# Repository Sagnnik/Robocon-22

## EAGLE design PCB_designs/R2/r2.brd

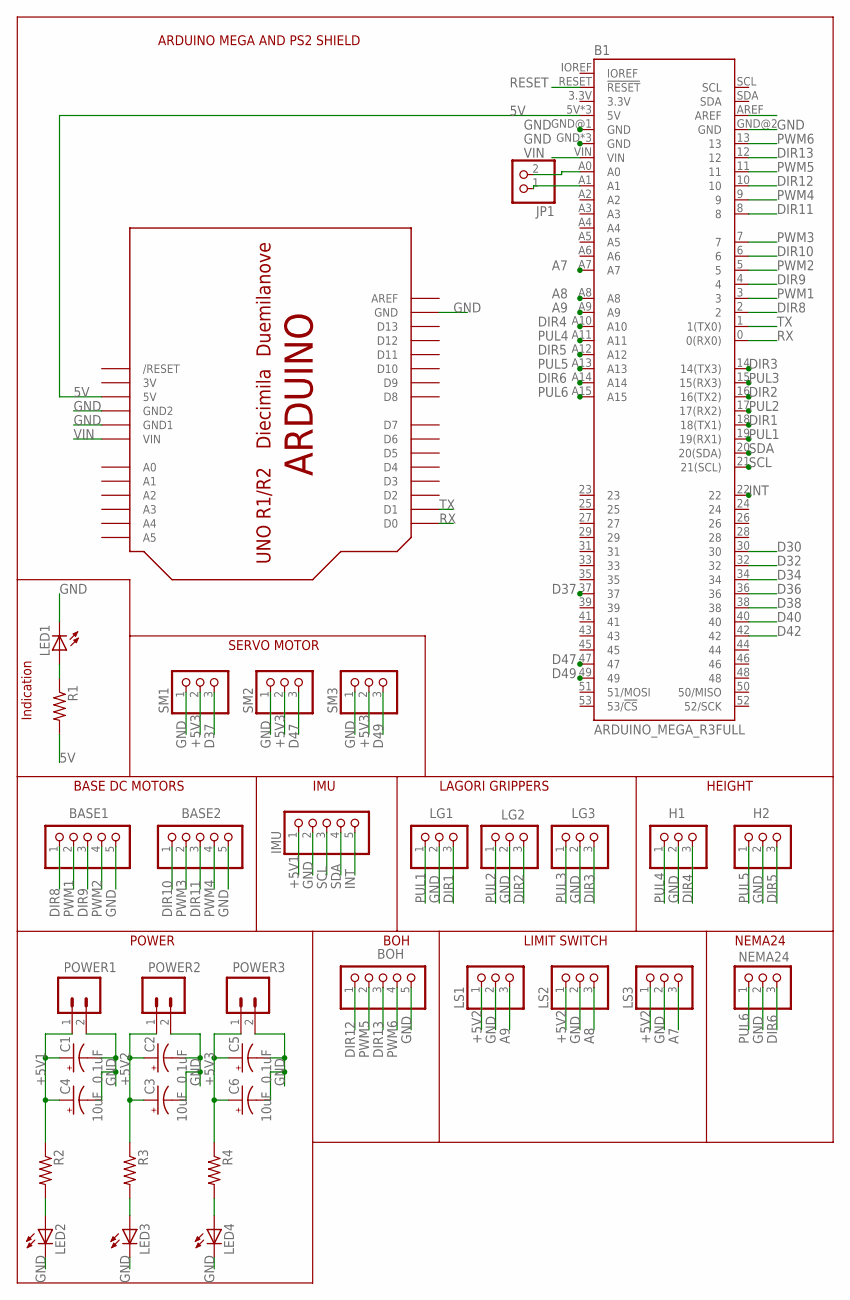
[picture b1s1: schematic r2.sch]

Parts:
B1: ARDUINO_MEGA_R3FULL; ARDUINO_MEGA_NO_SILK
BASE1, BASE2: PINHD-1X5; 1X05
BOH: PINHD-1X5; 1X05
C1, C2, C5: 0.1uF; E2-5
C3, C4, C6: 10uF; E2-5
H1, H2: PINHD-1X3; 1X03
IMU: PINHD-1X5; 1X05
JP1: PINHD-1X2; 1X02
LED1, LED2, LED3, LED4: LED3MM
LG1, LG2, LG3: PINHD-1X3; 1X03
LS1, LS2, LS3: PINHD-1X3; 1X03
NEMA24: PINHD-1X3; 1X03
POWER1, POWER2, POWER3: CONN_02; 1X02
R1, R2, R3, R4: R-US_0204/5; 0204/5
SM1, SM2, SM3: PINHD-1X3; 1X03
U$1: ARDUINO-NOHOLE

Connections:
3V: U$1.3V
5V: B1.5V, B1.5V@1 (5V), B1.5V@2 (5V), R1.2, U$1.5V
+5V1: C1.+, C4.+, IMU.1, POWER1.1, R2.1
+5V2: C2.+, C3.+, LS1.1, LS2.1, LS3.1, POWER2.1, R3.1
+5V3: C5.+, C6.+, POWER3.1, R4.1, SM1.2, SM2.2, SM3.2
A7: B1.A7, LS3.3
A8: B1.A8, LS2.3
A9: B1.A9, LS1.3
D30: B1.30
D32: B1.32
D34: B1.34
D36: B1.36
D37: B1.37, SM1.3
D38: B1.38
D40: B1.40
D42: B1.42
D47: B1.47, SM2.3
D49: B1.49, SM3.3
DIR1: B1.18 (18(TX1)), LG1.3
DIR2: B1.16 (16(TX2)), LG2.3
DIR3: B1.14 (14(TX3)), LG3.3
DIR4: B1.A10, H1.3
DIR5: B1.A12, H2.3
DIR6: B1.A14, NEMA24.3
DIR8: B1.2, BASE1.1
DIR9: B1.4, BASE1.3
DIR10: B1.6, BASE2.1
DIR11: B1.8, BASE2.3
DIR12: B1.10, BOH.1
DIR13: B1.12, BOH.3
GND: B1.GND, B1.GND@1 (GND), B1.GND@2 (GND), B1.GND@3 (GND), B1.GND@4 (GND), BASE1.5, BASE2.5, BOH.5, C1.-, C2.-, C3.-, C4.-, C5.-, C6.-, H1.2, H2.2, IMU.2, LED1.K (C), LED2.K (C), LED3.K (C), LED4.K (C), LG1.2, LG2.2, LG3.2, LS1.2, LS2.2, LS3.2, NEMA24.2, POWER1.2, POWER2.2, POWER3.2, SM1.1, SM2.1, SM3.1, U$1.GND, U$1.GND1, U$1.GND2
INT: B1.22, IMU.5
unnamed: LED1.A, R1.1
unnamed: B1.A0, JP1.2
unnamed: B1.A1, JP1.1
unnamed: LED3.A, R3.2
unnamed: LED4.A, R4.2
unnamed: LED2.A, R2.2
PUL1: B1.19 (19(RX1)), LG1.1
PUL2: B1.17 (17(RX2)), LG2.1
PUL3: B1.15 (15(RX3)), LG3.1
PUL4: B1.A11, H1.1
PUL5: B1.A13, H2.1
PUL6: B1.A15, NEMA24.1
PWM1: B1.3, BASE1.2
PWM2: B1.5, BASE1.4
PWM3: B1.7, BASE2.2
PWM4: B1.9, BASE2.4
PWM5: B1.11, BOH.2
PWM6: B1.13, BOH.4
RESET: B1.RESET (!RESET)
RX: B1.0 (0(RX0)), U$1.D0
SCL: B1.21 (21(SCL)), IMU.3
SDA: B1.20 (20(SDA)), IMU.4
TX: B1.1 (1(TX0)), U$1.D1
VIN: B1.VIN, U$1.VIN

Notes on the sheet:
POWER
BOH
LIMIT SWITCH
LAGORI GRIPPERS
BASE DC MOTORS
ARDUINO MEGA AND PS2 SHIELD
NEMA24
HEIGHT
Indication
IMU
SERVO MOTOR

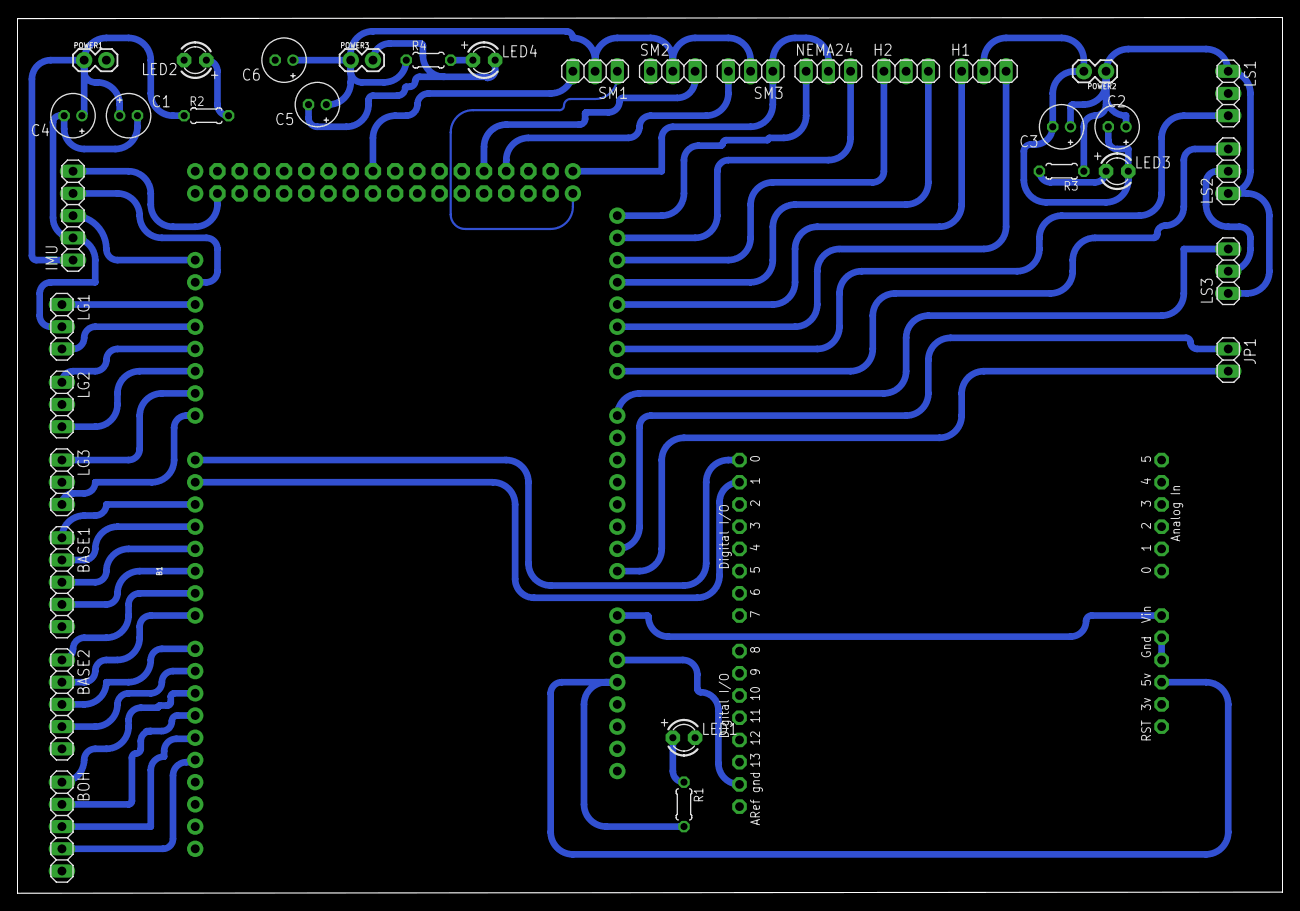
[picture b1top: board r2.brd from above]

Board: 2 copper layers, 144.6 x 100.1 mm, 36 parts (0 on the bottom side), 47 nets.

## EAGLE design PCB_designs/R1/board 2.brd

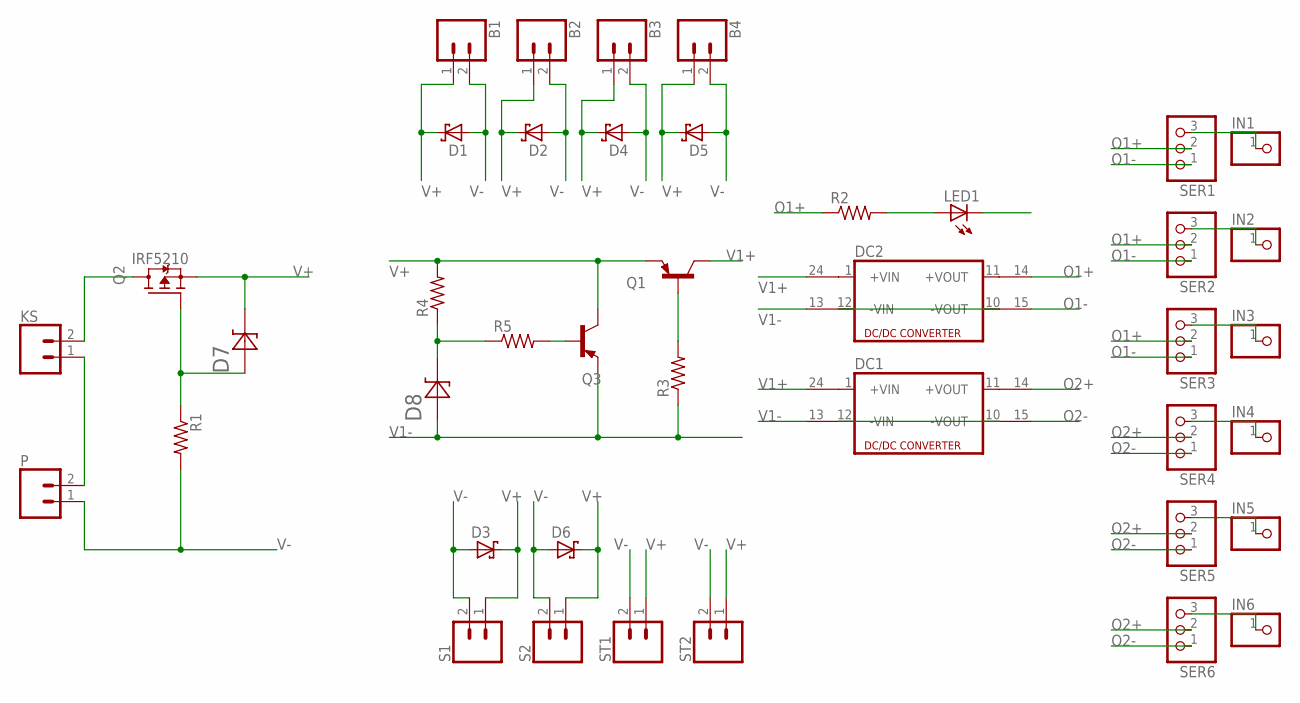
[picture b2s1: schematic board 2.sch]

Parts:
B1, B2, B3, B4: CONN_02; 1X02
D1, D2, D3, D4, D5, D6: SCHOTTKY-DIODEF126Z12; F126Z12
D7, D8: 1N4752A-T; DIOAD1060W80L410D260
DC1, DC2: DC213R; CMK
IN1, IN2, IN3, IN4, IN5, IN6: PINHD-1X1; 1X01
KS: CONN_02; 1X02
LED1: LED5MM
P: CONN_02; 1X02
Q1, Q3: 2N2907; TO92-EBC-OVAL
Q2: IRF5210; TO254P1054X469X2933-3
R1, R2, R3, R4, R5: R-US_0204/7; 0204/7
S1, S2: CONN_02; 1X02
SER1, SER2, SER3, SER4, SER5, SER6: PINHD-1X3; 1X03
ST1, ST2: CONN_02; 1X02

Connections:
unnamed: KS.1, P.2
unnamed: KS.2, Q2.2 (D)
unnamed: D7.A, Q2.1 (G), R1.1
unnamed: D8.C, R4.1, R5.1
unnamed: Q3.B, R5.2
unnamed: Q1.B, R3.2
unnamed: DC2.10 (-VOUT), DC2.12 (-VIN)
unnamed: DC1.10 (-VOUT), DC1.12 (-VIN)
unnamed: LED1.A, R2.2
unnamed: IN1.1, SER1.3
unnamed: IN2.1, SER2.3
unnamed: IN3.1, SER3.3
unnamed: IN4.1, SER4.3
unnamed: IN5.1, SER5.3
unnamed: IN6.1, SER6.3
O1+: DC2.14 (+VOUT1), R2.1, SER1.2, SER2.2, SER3.2
O1-: DC2.15 (-VOUT1), SER1.1, SER2.1, SER3.1
O2+: DC1.14 (+VOUT1), SER4.2, SER5.2, SER6.2
O2-: DC1.15 (-VOUT1), SER4.1, SER5.1, SER6.1
V1+: DC1.24 (+VIN1), DC2.24 (+VIN1), Q1.C
V1-: D8.A, DC1.13 (-VIN1), DC2.13 (-VIN1), Q3.E, R3.1
V+: B1.1, B2.1, B3.1, B4.1, D1.C, D2.C, D3.C, D4.C, D5.C, D6.C, D7.C, Q1.E, Q2.3 (S), Q3.C, R4.2, S1.1, S2.1, ST1.1, ST2.1
V-: B1.2, B2.2, B3.2, B4.2, D1.A, D2.A, D3.A, D4.A, D5.A, D6.A, P.1, R1.2, S1.2, S2.2, ST1.2, ST2.2

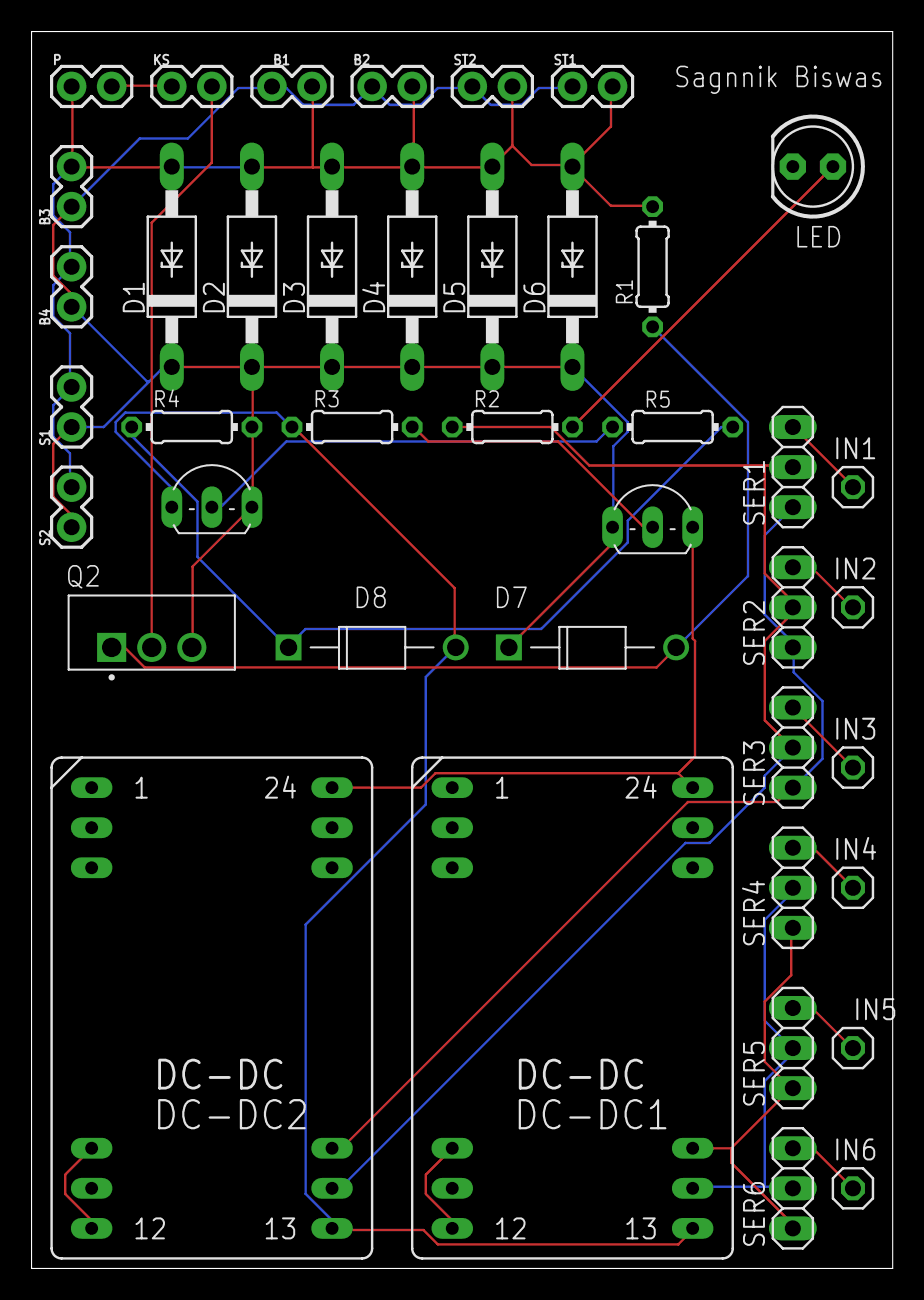
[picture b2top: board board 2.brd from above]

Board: 2 copper layers, 54.6 x 78.4 mm, 41 parts (0 on the bottom side), 23 nets.

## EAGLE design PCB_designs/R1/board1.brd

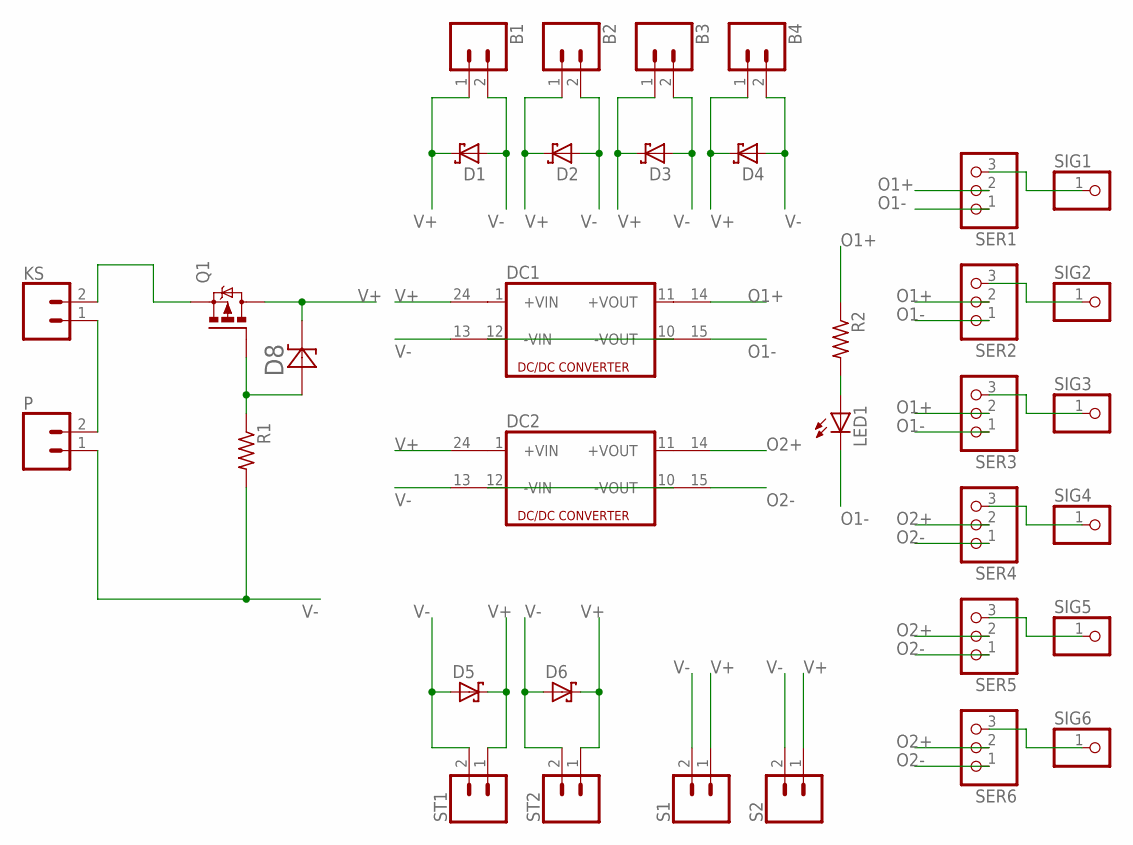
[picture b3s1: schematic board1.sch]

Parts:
B1, B2, B3, B4: CONN_02; 1X02
D1, D2, D3, D4, D5, D6: SCHOTTKY-DIODEAG; AG
D8: 1N4752A-T; DIOAD1060W80L410D260
DC1, DC2: DC213R; CMK
KS: CONN_02; 1X02
LED1: LED5MM
P: CONN_02; 1X02
Q1: IRF9530; TO220BV
R1, R2: R-US_0207/10; 0207/10
S1, S2: CONN_02; 1X02
SER1, SER2, SER3, SER4, SER5, SER6: PINHD-1X3; 1X03
SIG1, SIG2, SIG3, SIG4, SIG5, SIG6: PINHD-1X1; 1X01
ST1, ST2: CONN_02; 1X02

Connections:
unnamed: KS.1, P.2
unnamed: D8.A, Q1.G, R1.1
unnamed: KS.2, Q1.S
unnamed: LED1.A, R2.2
unnamed: DC1.10 (-VOUT), DC1.12 (-VIN)
unnamed: DC2.10 (-VOUT), DC2.12 (-VIN)
unnamed: SER1.3, SIG1.1
unnamed: SER2.3, SIG2.1
unnamed: SER3.3, SIG3.1
unnamed: SER4.3, SIG4.1
unnamed: SER5.3, SIG5.1
unnamed: SER6.3, SIG6.1
O1+: DC1.14 (+VOUT1), R2.1, SER1.2, SER2.2, SER3.2
O1-: DC1.15 (-VOUT1), LED1.K (C), SER1.1, SER2.1, SER3.1
O2+: DC2.14 (+VOUT1), SER4.2, SER5.2, SER6.2
O2-: DC2.15 (-VOUT1), SER4.1, SER5.1, SER6.1
V+: B1.1, B2.1, B3.1, B4.1, D1.C, D2.C, D3.C, D4.C, D5.C, D6.C, D8.C, DC1.24 (+VIN1), DC2.24 (+VIN1), Q1.D, S1.1, S2.1, ST1.1, ST2.1
V-: B1.2, B2.2, B3.2, B4.2, D1.A, D2.A, D3.A, D4.A, D5.A, D6.A, DC1.13 (-VIN1), DC2.13 (-VIN1), P.1, R1.2, S1.2, S2.2, ST1.2, ST2.2

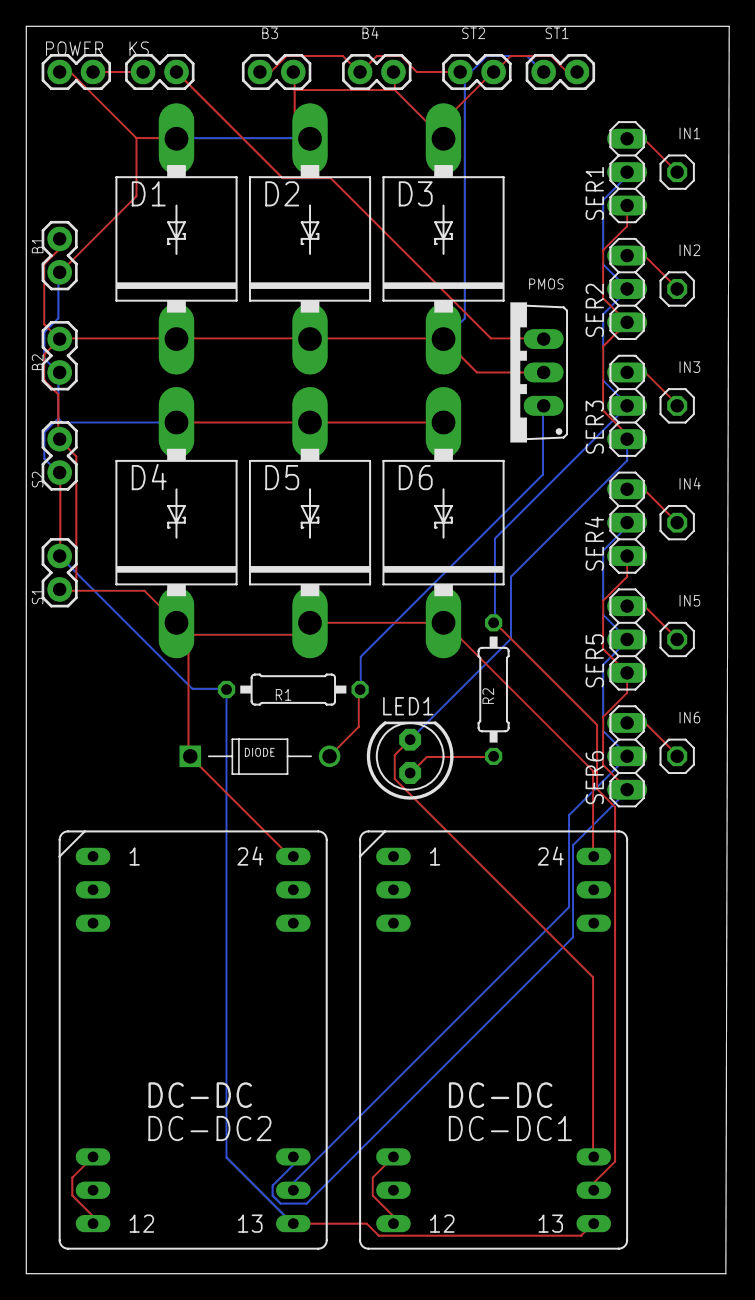
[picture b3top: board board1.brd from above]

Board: 2 copper layers, 53.5 x 94.9 mm, 35 parts (0 on the bottom side), 18 nets.

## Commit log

2022-08-16 PCB designs
2022-08-16 Custom YOLOv3 model for the aiming mechanism

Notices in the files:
parts and their libraries:
SparkFun-Connectors: Licensing: Creative Commons ShareAlike 4.0 International - https://creativecommons.org/licenses/by-sa/4.0
